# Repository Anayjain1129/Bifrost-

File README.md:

# Bifrost-

# Zine-Page

### What is this project? 
This is a Split Keyboard made by a 15 year old teenager(me) from india. it uses XIAO nRF52840 as MCU and a battery connection too! which uses ZMK in firmware! 

### How to use/build it?
1. Break the PCB in 2 halves! 
2. Assemble the PCB with soldering iron by soldering the MCU, switches, and diodes
3. Plug in the MCU with PCB and then put the firmware file in it
4. Drag and drop the firmware file in the MCU  
5. Do the same things with other XIAO 
6. That's now you have your split keyboard working
7. Make sure to put it in an enclosure

### Why did i made this? 
I made this project to learn how does the XIAO-nRF52840-SMD MCUs work and how does the battery work with the PCBs and also to learn how to solder the SMD components, as they are so small in size and to master the soldering of componentes by hand.

### What was the Hardrest part?
All of the parts were hard and i think i learned so much from this project too! but using ZMK was the hardest part! but yea making this project did helped me to learn alot! 

# Features
- Seeed Studio XIAO 
- Custom Layout
- ZMK firmware
- Very cool case/enclosure to hold the PCB
- Uses nRF52840
- Uses magnets to keep things together

## Schematics 

## PCB

## 3d PCB

# Case
## Top

## Bottom

# 3d view of all parts together

# BOM
| Item | Description | Quantity | Unit Price (INR) | Total Price (INR) | Total Price (USD) | URL |
|------|-------------|----------|-----------------|-------------------|-------------------|-----|
| PCB | Printed Circuit Board | 5 | ₹834 | ₹4,170 | $44.18 | N/A |
| Seeed XIAO nRF52840 | Microcontroller | 2 | ₹1,152 | ₹2,304 | $24.41 | [Robu.in](https://robu.in/product/seeed-studio-xiao-ble-nrf52840/?gad_source=1&gad_campaignid=17416544847&gbraid=0AAAAADvLFWeP63tfJcREqEEJOvF9pKHih&gclid=CjwKCAjw9NjRBhATEiwA_p2J8QqYpS8QPFfUIue8c5T7P2aq6sJovGVlfgAdk8MTvIrfn7f6xPkeKBoCx_EQAvD_BwE) |
| Gateron Hotswap Sockets | Switch Sockets | 43 | ₹10 | ₹430 | $4.56 | [StacksKB](https://stackskb.com/store/gateron-hotswap-sockets/) |
| Cherry MX Switches | Switch | 50 | ₹18 | ₹900 | $9.54 | [Neomacro](https://neomacro.in/products/gateron-ef-cedar) |
| Blank DSA Keycaps 1u | Keycaps | 50 | ₹18.88 | ₹944 | $10.00 | [MecKeys](https://meckeys.com/shop/accessories/keyboard-accessories/keycaps/blank/blank-dsa-keycaps-1u/) |
| 3.7V LiPo Battery | Battery | 1 | ₹293 | ₹293 | $3.10 | [Amazon.in](https://www.amazon.in/Bhajanlal-Greenery-Rechargeable-Lithium-Batteries/dp/B0CYQ6H8FW?sr=8-3) |
| 1N4148WS SOD-123 | Diodes | 50 | ₹3 | ₹150 | $1.59 | [QuartzComponents](https://quartzcomponents.com/products/1n4148ws-t4-switching-diode-sod-123-smd-package?variant=45540031627498) |
| **TOTAL** | | | | **₹9,191** | **$97.38** | |

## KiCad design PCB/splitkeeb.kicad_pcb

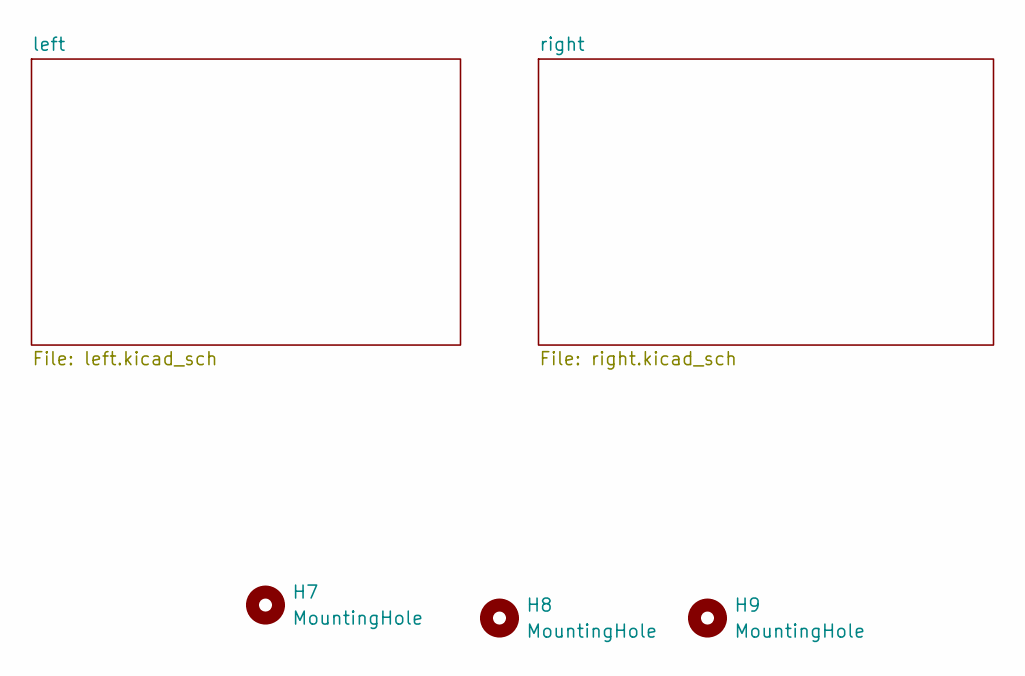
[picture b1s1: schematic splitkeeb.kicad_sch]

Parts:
H7, H8, H9: MountingHole; mouse-bite-2mm-slot

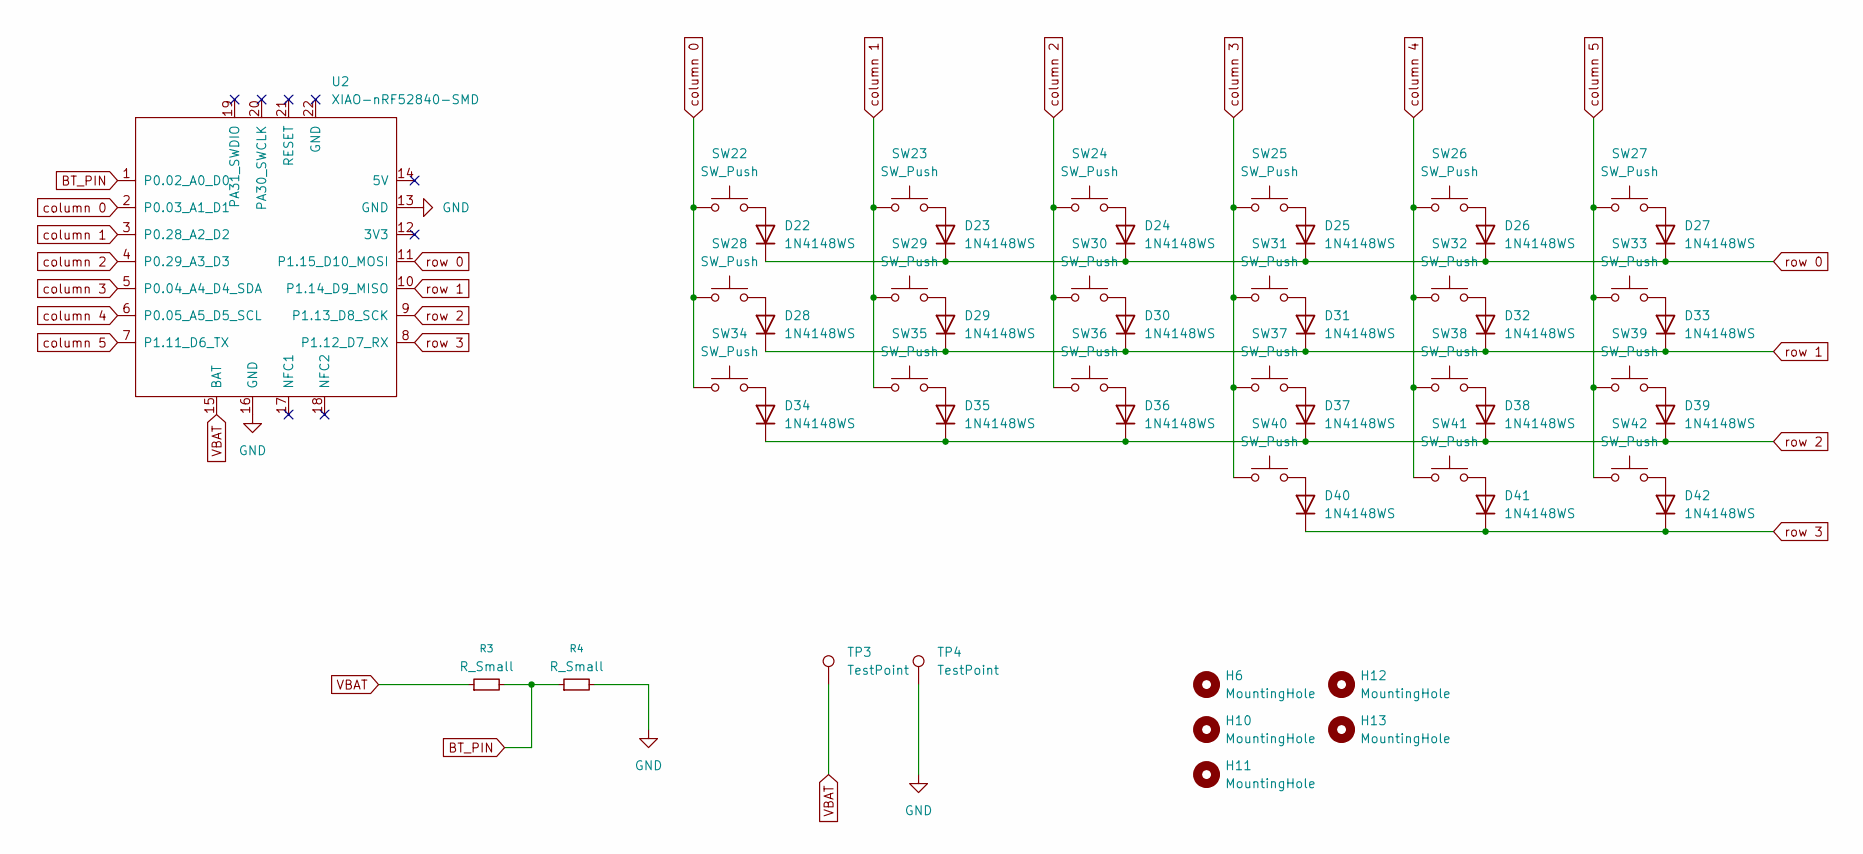
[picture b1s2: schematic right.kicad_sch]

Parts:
D22, D23, D24, D25, D26, D27, D28, D29, D30, D31, D32, D33, D34, D35, D36, D37, D38, D39, D40, D41, D42: 1N4148WS; D_SOD-323
H6, H10, H11, H12, H13: MountingHole; MountingHole_2.2mm_M2
R3, R4: R_Small; R_0805_2012Metric
SW22, SW23, SW24, SW25, SW26, SW27, SW28, SW29, SW30, SW31, SW32, SW33, SW34, SW35, SW36, SW37, SW38, SW39, SW40, SW41, SW42: SW_Push; Hotswap_MX_1.00u
TP3, TP4: TestPoint; TestPoint_Pad_D2.0mm
U2: XIAO-nRF52840-SMD; modified-XIAO-nRF52840-SMD

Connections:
BT_PIN: R3.2, R4.1, U2.1 (P0.02_A0_D0); also elsewhere on the board
GND: R4.2, TP4.1 (1_1), U2.13 (GND), U2.16 (GND); also elsewhere on the board
unnamed: D22.2 (A), SW22.2
unnamed: D23.2 (A), SW23.2
unnamed: D24.2 (A), SW24.2
unnamed: D25.2 (A), SW25.2
unnamed: D26.2 (A), SW26.2
unnamed: D27.2 (A), SW27.2
unnamed: D28.2 (A), SW28.2
unnamed: D29.2 (A), SW29.2
unnamed: D30.2 (A), SW30.2
unnamed: D31.2 (A), SW31.2
unnamed: D32.2 (A), SW32.2
unnamed: D33.2 (A), SW33.2
unnamed: D34.2 (A), SW34.2
unnamed: D35.2 (A), SW35.2
unnamed: D36.2 (A), SW36.2
unnamed: D37.2 (A), SW37.2
unnamed: D38.2 (A), SW38.2
unnamed: D39.2 (A), SW39.2
unnamed: D40.2 (A), SW40.2
unnamed: D41.2 (A), SW41.2
unnamed: D42.2 (A), SW42.2
VBAT: R3.1, TP3.1 (1_1), U2.15 (BAT); also elsewhere on the board
column 0: SW22.1, SW28.1, SW34.1, U2.2 (P0.03_A1_D1); also elsewhere on the board
column 1: SW23.1, SW29.1, SW35.1, U2.3 (P0.28_A2_D2); also elsewhere on the board
column 2: SW24.1, SW30.1, SW36.1, U2.4 (P0.29_A3_D3); also elsewhere on the board
column 3: SW25.1, SW31.1, SW37.1, SW40.1, U2.5 (P0.04_A4_D4_SDA); also elsewhere on the board
column 4: SW26.1, SW32.1, SW38.1, SW41.1, U2.6 (P0.05_A5_D5_SCL); also elsewhere on the board
column 5: SW27.1, SW33.1, SW39.1, SW42.1, U2.7 (P1.11_D6_TX); also elsewhere on the board
row 0: D22.1 (K), D23.1 (K), D24.1 (K), D25.1 (K), D26.1 (K), D27.1 (K), U2.11 (P1.15_D10_MOSI); also elsewhere on the board
row 1: D28.1 (K), D29.1 (K), D30.1 (K), D31.1 (K), D32.1 (K), D33.1 (K), U2.10 (P1.14_D9_MISO); also elsewhere on the board
row 2: D34.1 (K), D35.1 (K), D36.1 (K), D37.1 (K), D38.1 (K), D39.1 (K), U2.9 (P1.13_D8_SCK); also elsewhere on the board
row 3: D40.1 (K), D41.1 (K), D42.1 (K), U2.8 (P1.12_D7_RX); also elsewhere on the board

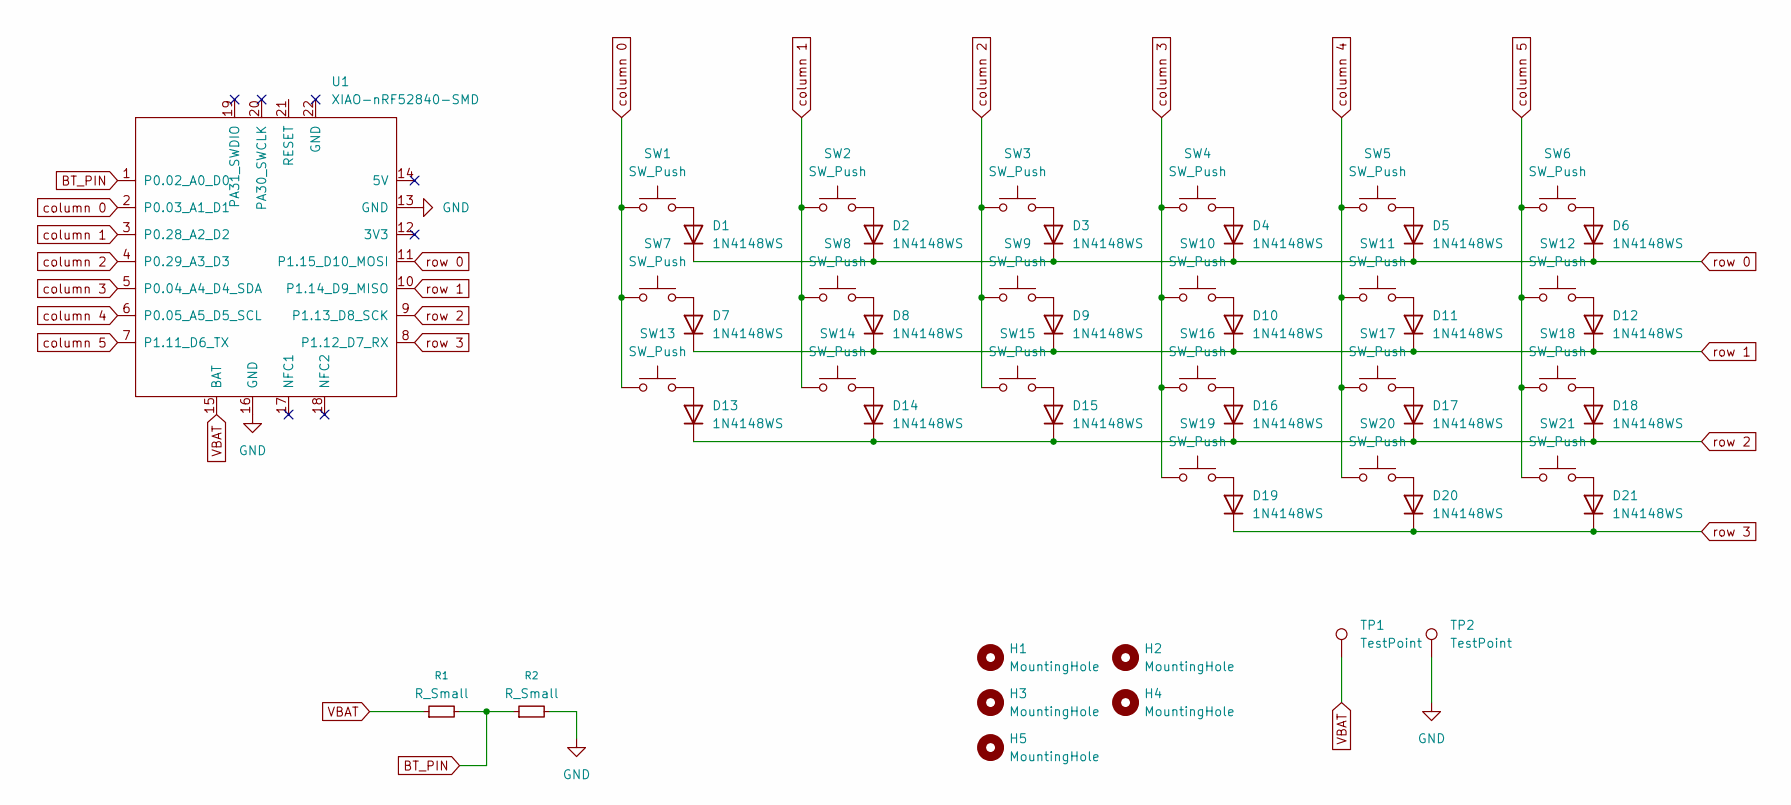
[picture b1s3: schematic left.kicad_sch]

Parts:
D1, D2, D3, D4, D5, D6, D7, D8, D9, D10, D11, D12, D13, D14, D15, D16, D17, D18, D19, D20, D21: 1N4148WS; D_SOD-323
H1, H2, H3, H4, H5: MountingHole; MountingHole_2.2mm_M2
R1, R2: R_Small; R_0805_2012Metric
SW1, SW2, SW3, SW4, SW5, SW6, SW7, SW8, SW9, SW10, SW11, SW12, SW13, SW14, SW15, SW16, SW17, SW18, SW19, SW20, SW21: SW_Push; Hotswap_MX_1.00u
TP1, TP2: TestPoint; TestPoint_Pad_D2.0mm
U1: XIAO-nRF52840-SMD; modified-XIAO-nRF52840-SMD

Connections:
BT_PIN: R1.2, R2.1, U1.1 (P0.02_A0_D0); also elsewhere on the board
GND: R2.2, TP2.1 (1_1), U1.13 (GND), U1.16 (GND); also elsewhere on the board
unnamed: D1.2 (A), SW1.2
unnamed: D2.2 (A), SW2.2
unnamed: D3.2 (A), SW3.2
unnamed: D4.2 (A), SW4.2
unnamed: D5.2 (A), SW5.2
unnamed: D6.2 (A), SW6.2
unnamed: D7.2 (A), SW7.2
unnamed: D8.2 (A), SW8.2
unnamed: D9.2 (A), SW9.2
unnamed: D10.2 (A), SW10.2
unnamed: D11.2 (A), SW11.2
unnamed: D12.2 (A), SW12.2
unnamed: D13.2 (A), SW13.2
unnamed: D14.2 (A), SW14.2
unnamed: D15.2 (A), SW15.2
unnamed: D16.2 (A), SW16.2
unnamed: D17.2 (A), SW17.2
unnamed: D18.2 (A), SW18.2
unnamed: D19.2 (A), SW19.2
unnamed: D20.2 (A), SW20.2
unnamed: D21.2 (A), SW21.2
VBAT: R1.1, TP1.1 (1_1), U1.15 (BAT); also elsewhere on the board
column 0: SW1.1, SW7.1, SW13.1, U1.2 (P0.03_A1_D1); also elsewhere on the board
column 1: SW2.1, SW8.1, SW14.1, U1.3 (P0.28_A2_D2); also elsewhere on the board
column 2: SW3.1, SW9.1, SW15.1, U1.4 (P0.29_A3_D3); also elsewhere on the board
column 3: SW4.1, SW10.1, SW16.1, SW19.1, U1.5 (P0.04_A4_D4_SDA); also elsewhere on the board
column 4: SW5.1, SW11.1, SW17.1, SW20.1, U1.6 (P0.05_A5_D5_SCL); also elsewhere on the board
column 5: SW6.1, SW12.1, SW18.1, SW21.1, U1.7 (P1.11_D6_TX); also elsewhere on the board
row 0: D1.1 (K), D2.1 (K), D3.1 (K), D4.1 (K), D5.1 (K), D6.1 (K), U1.11 (P1.15_D10_MOSI); also elsewhere on the board
row 1: D7.1 (K), D8.1 (K), D9.1 (K), D10.1 (K), D11.1 (K), D12.1 (K), U1.10 (P1.14_D9_MISO); also elsewhere on the board
row 2: D13.1 (K), D14.1 (K), D15.1 (K), D16.1 (K), D17.1 (K), D18.1 (K), U1.9 (P1.13_D8_SCK); also elsewhere on the board
row 3: D19.1 (K), D20.1 (K), D21.1 (K), U1.8 (P1.12_D7_RX); also elsewhere on the board

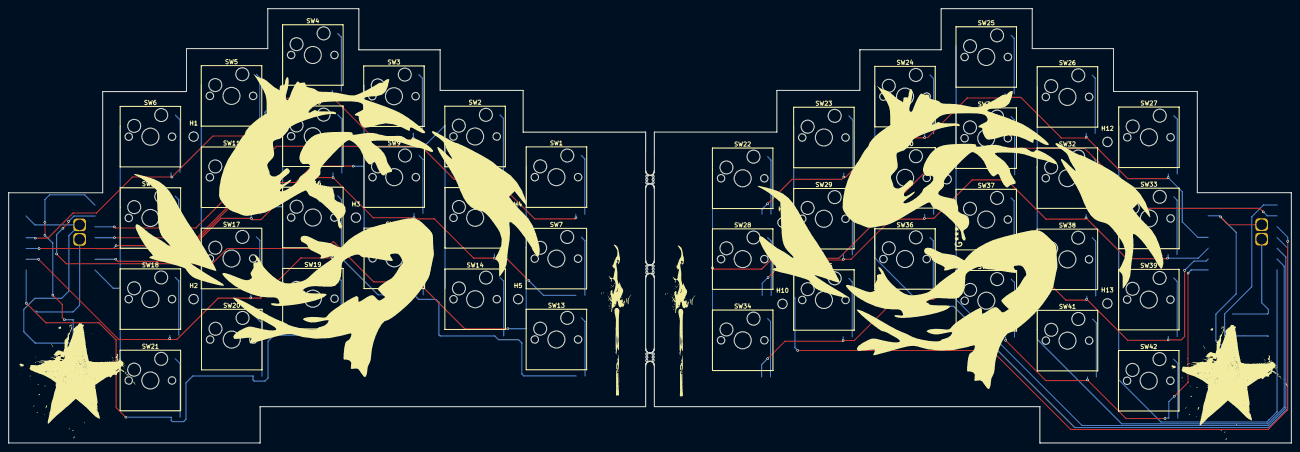
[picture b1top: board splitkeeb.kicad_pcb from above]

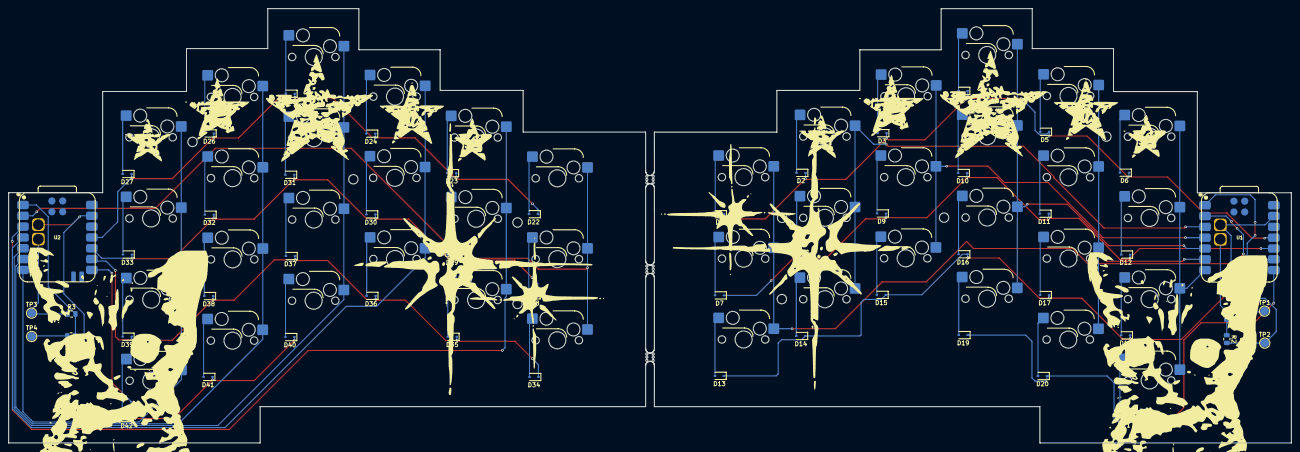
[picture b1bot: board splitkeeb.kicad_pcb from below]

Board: 2 copper layers, 301.1 x 102.0 mm, 107 parts (52 on the bottom side), 55 nets.

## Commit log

2026-06-20 case files
2026-06-20 added the gerber files
2026-06-20 Add image to README for Bifrost keyboard
2026-06-20 Add Zine-Page section with image to README
2026-06-20 Enhance README with additional images
    Added multiple images to the README for better visualization.
2026-06-20 Enhance README with project details and instructions
    Added project description, usage instructions, and features.
2026-06-20 Add Bill of Materials section to README
    Added a Bill of Materials (BOM) section with item details and pricing.
2026-06-20 Remove Bill of Materials section from README
    Removed the Bill of Materials section from the README.
2026-06-20 Remove one image from README
    Removed an image from the README.
2026-06-20 Update README with hardest part of the project
    Added a section about the hardest part of the project.
2026-06-20 Create Firmware
2026-06-25 Update README with new images and project info
    Added new images and updated project details in the README.
2026-06-25 Update README.md with additional images
    Added new images to the README file.
2026-06-25 Add images to 3d PCB section in README
    Added new images to the 3d PCB section of the README.
2026-06-25 Add additional images to README
